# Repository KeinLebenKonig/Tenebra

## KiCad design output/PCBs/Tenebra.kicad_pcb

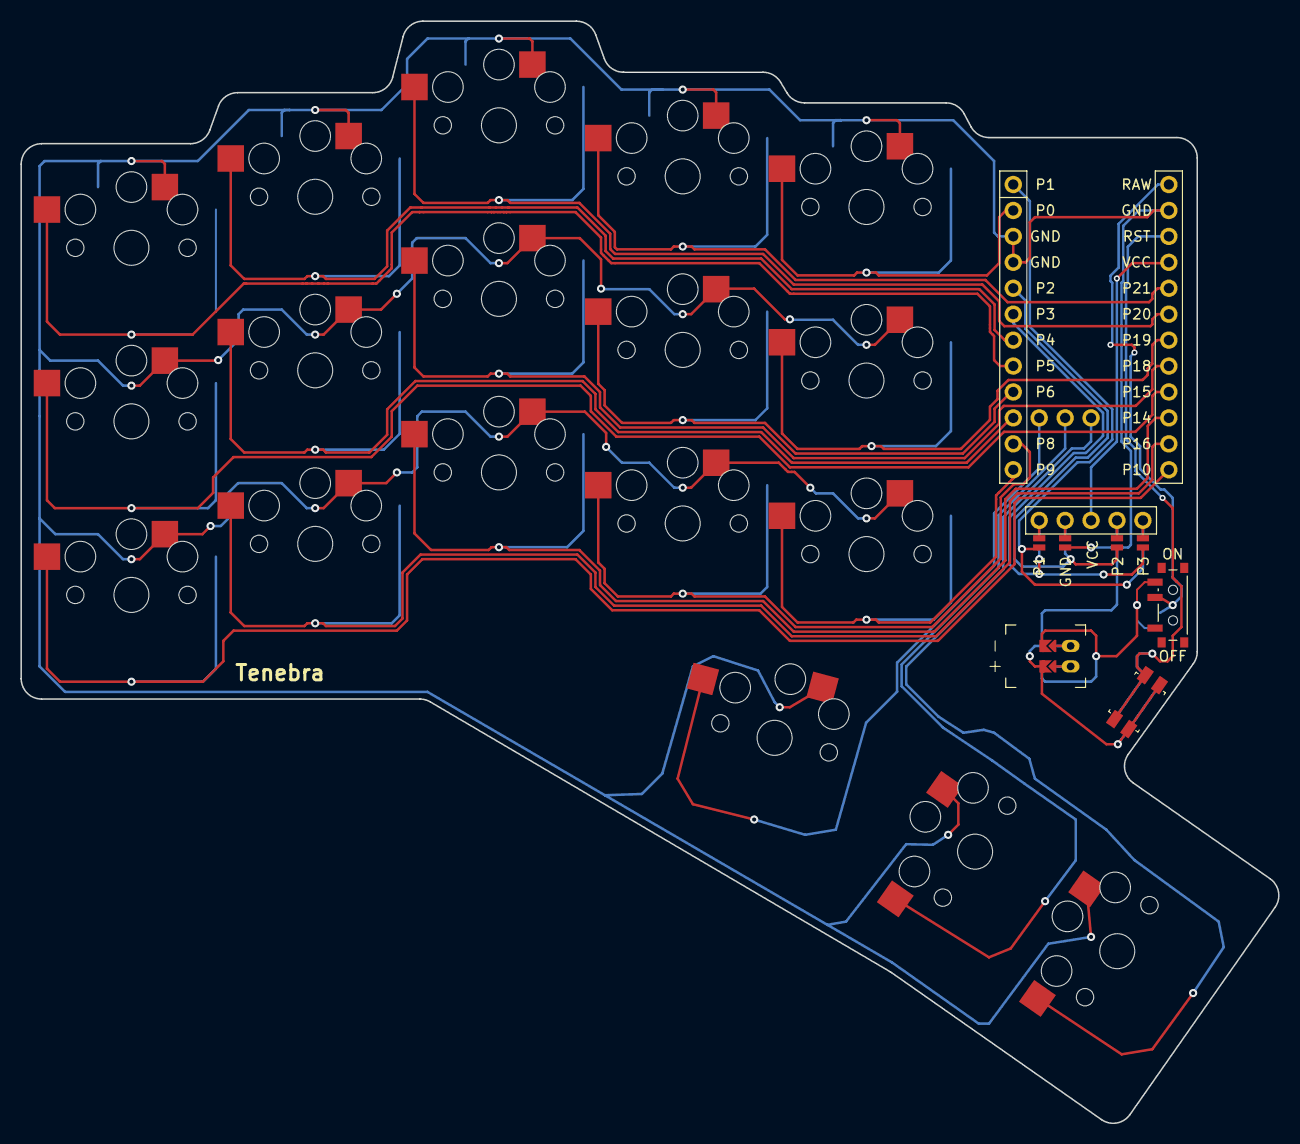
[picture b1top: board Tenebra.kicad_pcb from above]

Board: 2 copper layers, 123.2 x 108.0 mm, 23 parts (0 on the bottom side), 32 nets.

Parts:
DISP1: display_nice_view
JST1: battery_connector_jst_ph_2
MCU1: mcu_nice_nano
PWR1: power_switch_smd_side
RST1: reset_switch_smd_side
S1, S2, S3, S4, S5, S6, S7, S8, S9, S10, S11, S12, S13, S14, S15, S16, S17, S18: PG1350

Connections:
DISP1_1: DISP1.1, DISP1.14, DISP1.27
DISP1_2: DISP1.2, DISP1.15, DISP1.26
DISP1_4: DISP1.4, DISP1.16, DISP1.25
DISP1_5: DISP1.5, DISP1.17, DISP1.24
GND: DISP1.11, DISP1.21, JST1.2, MCU1.2, MCU1.21, MCU1.22, RST1.1, RST1.3, S1.1, S2.1, S3.1, S4.1, S5.1, S6.1, S7.1, S8.1, S9.1, S10.1, S11.1, S12.1, S13.1, S14.1, S15.1, S16.1, S17.1, S18.1
JST1_1: JST1.11, JST1.21, JST1.31
JST1_2: JST1.12, JST1.22, JST1.32
P1: DISP1.10, DISP1.20, MCU1.24
P2: DISP1.12, DISP1.22, MCU1.20
P3: DISP1.13, DISP1.23, MCU1.19
RAW: MCU1.1, PWR1.2
RST: MCU1.3, RST1.2, RST1.4
VCC: DISP1.3, MCU1.4
main_index_bottom: MCU1.14, S10.2
main_index_home: MCU1.16, S11.2
main_index_top: MCU1.5, S12.2
main_inner_bottom: MCU1.13, S13.2
main_inner_home: MCU1.7, S14.2
main_inner_top: MCU1.23, S15.2
main_middle_bottom: MCU1.10, S7.2
main_middle_home: MCU1.8, S8.2
main_middle_top: MCU1.6, S9.2
main_pinky_bottom: MCU1.12, S1.2
main_pinky_home: MCU1.9, S2.2
main_pinky_top: MCU1.17, S3.2
main_ring_bottom: MCU1.11, S4.2
main_ring_home: MCU1.15, S5.2
main_ring_top: MCU1.18, S6.2
pos: JST1.1, PWR1.3
thumb_home: MCU1.26, S17.2
thumb_inner: MCU1.25, S16.2
thumb_outer: MCU1.27, S18.2

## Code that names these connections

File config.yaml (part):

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                -   ref: thumb_home
                    shift: [-0.8cx, -0cy]

                -   ref: main_pinky_bottom
                    shift: [1.6cx, -0.6cy]
                -   ref: main_pinky_bottom
                    shift: [0.6cx, -0.6cy]
                -   ref: main_pinky_bottom
                    shift: [-0.6cx, -0.6cy]

                -   ref: main_pinky_top
                    shift: [-0.6cx, 0.6cy]
                -   ref: main_pinky_top
                    shift: [0.4cx, 0.6cy]

                -   ref: main_ring_top
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                -   ref: thumb_home
                    shift: [-0.8cx, -0cy]

                -   ref: main_pinky_bottom
                    shift: [1.6cx, -0.6cy]
                -   ref: main_pinky_bottom
                    shift: [0.6cx, -0.6cy]
                -   ref: main_pinky_bottom
                    shift: [-0.6cx, -0.6cy]

                -   ref: main_pinky_top
                    shift: [-0.6cx, 0.6cy]
                -   ref: main_pinky_top
                    shift: [0.4cx, 0.6cy]

                -   ref: main_ring_top
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                -   ref: thumb_home
                    shift: [-0.8cx, -0cy]

                -   ref: main_pinky_bottom
                    shift: [1.6cx, -0.6cy]
                -   ref: main_pinky_bottom
                    shift: [-0.6cx, -0.6cy]

                -   ref: main_pinky_top
                    shift: [-0.6cx, 0.6cy]
                -   ref: main_pinky_top
                    shift: [0.4cx, 0.6cy]

                -   ref: main_ring_top
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          P21: main_index_top
          P20: main_middle_top
          P4: main_ring_top
          P5: main_pinky_top

          P19: main_inner_home
          P6: main_index_home
          P18: main_middle_home
          P7: main_ring_home
          P15: main_pinky_home

          P9: main_inner_bottom
          P8: main_index_bottom
          P14: main_middle_bottom
          P16: main_ring_bottom
          P10: main_pinky_bottom

          P101: thumb_inner
          P102: thumb_home
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
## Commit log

2025-03-07 Started work on pin assignments
2025-03-14 generated kicad and gerber files
2025-03-14 Working on cases
2025-05-03 mirrored for v2?
